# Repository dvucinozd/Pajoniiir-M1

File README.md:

# Pajoniiir-M1

Purpose-built Rev A mainboard for the **Pajoniiir standalone dual-deck DJ system**.

This repository contains the live hierarchical KiCad design, electrical and firmware contracts, mechanical evidence, placement/routing screening contracts, local CAD libraries and fail-closed validation tools.

## Current status

**Electrical milestone:** M1-ELEC-B2

**Mechanical milestone:** M1-MECH-B7

**Pre-layout milestone:** M1-PRELAYOUT-B10 - routed ESP32-P4 flash, crystal and external-DCDC feasibility proof

**Schematic structure:** PASS — 15/15 leaf sheets

**KiCad toolchain:** KiCad 10 only; local KiCad 10.0.4 ERC passes with zero violations and CI installs the KiCad 10 stable release

**Manufacturing BOM parity:** PASS — 244 source / 244 exported, 15 DNP, 3 intentional blank footprints

**Board-first mechanical contract:** PASS — display profiles cannot define the PCB outline or mounts

**Display-derived B2-B6 geometry:** historical screening only

**Final placement/routing freeze:** BLOCKED — 12 physical/EVT gates remain

**Gerber/EVT order:** NOT AUTHORIZED

Evidence updates: [ERC/library closure](docs/Pajoniiir_M1_ERC_Library_Closure_2026-09-04.md), [DSI506 rear image and corrected height](docs/Pajoniiir_M1_DSI506_Evidence_2026-09-04.md).

The current human-readable snapshot is [Pajoniiir M1 Current Design Status B10](docs/Pajoniiir_M1_Current_Design_Status_B10.md).

## Architecture

```text
                         5 V LOCKING INPUT
                                |
                         TPS259474 eFuse
                                |
                         5V_PROTECTED
                                |
                    5 mOhm Kelvin system shunt
                       / INA238 measurement
                                |
                             5V_SYS
              +-----------------+------------------+
              |                                    |
          TPS62132                         USB VBUS switches
          3V3_SYS                          TPS25221 x2
              |                               |       |
      +-------+---------+                  USB0 HS  USB1 FS
      |       |         |                  storage   FLX4
      v       v         v
  ESP32-P4 ESP32-C6  PCM5102A
      |      SDIO      MAIN L/R
      |
      +-- 15-pin MIPI DSI + I2C --> qualified display profile
      +-- SDMMC -----------------> microSD
```

The mainboard exposes a generic 15-pin Raspberry-Pi-style MIPI DSI host interface. EYOYO DSI506 / DYL0023 is the first validated display profile; other models may use the same board after electrical, power, firmware and cable qualification.

## Electrical baseline

- ESP32-P4NRW32X, target silicon v3.2 or newer approved revision
- 32 MB in-package PSRAM
- W25Q128JVPIQ 16 MB external QSPI flash
- ESP32-C6-WROOM-1-N4 over four-bit SDIO
- USB0 dedicated High-Speed storage host
- USB1 GPIO26/27 Full-Speed DDJ-FLX4 MIDI/UAC host
- independent TPS25221 VBUS switching, about 1.0 A USB0 and 1.6 A USB1 initial limits
- PCM5102APWR stereo MAIN output with deterministic XSMT boot mute
- native four-bit SDMMC microSD with TPS22918 power cycling
- P4 UART, P4 USB Serial/JTAG pogo and C6 recovery paths
- optional INA238 system power telemetry

## DSI host contract

```text
Host connector    Amphenol SFW15R-2STE1LF
Interface         15 contacts, 1.0 mm, Raspberry-Pi-style DSI map
Supply branch     3V3_DISPLAY_MODULE; final multi-model budget open
DSI routing       clock + lane0 + lane1
I2C               GPIO7 SDA / GPIO8 SCL
Cable             qualified per display model or adapter
Validated profile DSI506 / DYL0023: lane0, 800 Mbps, RGB888, 27.777 MHz
```

Connector shape alone does not prove compatibility. Every supported display needs a recorded pin map, power envelope, DSI timing/controller profile and cable orientation.

## Mechanical baseline

The mainboard is a standalone assembly and mounts to its own chassis or enclosure bosses. Its outline, mounting pattern and connector coordinates remain open until complete footprint packing, routing, thermal and service-envelope work establishes a viable board.

DSI506-derived values such as the 58 x 49 mm rear posts, 104 x 62 mm board screen and 128 x 84 x 30 mm enclosure screen are retained only for optional DSI506 bracket/enclosure work. They are not production `Edge.Cuts` authority.

## Connector and footprint state

| RefDes | Production part | Footprint | Mechanical state |
|---|---|---|---|
| J1 | Switchcraft 722RAHLP | open | terminal-center and panel geometry required |
| J2/J3 | Amphenol 87520-1010ALF | locked | panel/cable envelope open |
| J4/J5 | Kycon KLPX-0848A-2-W-G / -R-G | locked | panel/cable envelope open |
| J6 | Amphenol SFW15R-2STE1LF | locked | board-edge placement, power budget and per-display cable profile open |
| J7 | Molex 503398-1892 | locked | slot/access/clearance open |
| SW1/SW2 | B3U-3000P-B | locked | recessed tool-hole placement open |
| J9 | project-local factory pogo | closed, DNL | normal placement work only |

Only `J1`, `C3` and `C8` intentionally have blank footprints in the manufacturing source.

## PCB and routing state

`hardware/Pajoniiir-M1/Pajoniiir-M1.kicad_pcb` is a populated four-copper-layer pre-layout canvas. It contains all 244 assigned footprints and 193 named schematic nets in eight `Dwgs.User` working domains. B10 adds 78 track segments and 11 vias for the P4 external flash, crystal and external-DCDC proof. The P4 group has no footprint bounding-box overlaps; the board still has no zones or `Edge.Cuts`.

`m1_board_packing_inventory_b7.json` records all 247 schematic components, 244 assigned footprints, 33 footprint classes including the blank-gate class, and the seven board-first packing phases.

`m1_board_placement_seed_b8.json` records the generated domain coordinates and explicitly marks every coordinate as non-production. The seed and validator scripts preserve schematic UUID paths so KiCad can continue synchronizing the board with the hierarchy.

`m1_prelayout_b9_core_island.json` remains the reproducible unrouted source placement. `m1_prelayout_b10_core_routes.json` records the live critical routes and metrics. Its validator enforces the 5.203 mm U1/Y1 body gap, QSPI transition topology, 0.60/0.30 mm B10 vias, power-trunk widths, zero P4 bounding-box overlaps and zero route-geometry DRC violations.

The stackup is locked to JLCPCB `JLC04161H-7628`, 1.6 mm, 1 oz outer copper and 0.5 oz inner copper.

```text
F.Cu   components + critical USB/MIPI/QSPI/SDIO routing
In1.Cu continuous solid GND reference
In2.Cu power distribution + compatible low-speed routing
B.Cu   secondary components and low-speed routing
```

B5 locks routing topology and provides screening geometry:

- USB: 90 ohm differential; screening 0.2332 mm width / 0.15 mm gap
- MIPI: 100 ohm differential; screening 0.1722 mm width / 0.15 mm gap

These numbers are not production impedance locks. Exact JLCPCB calculator records, soldermask/model selection and matching KiCad rules are required before route freeze.

## Open layout blockers

The current 12 blocking gates are:

```text
C3_INPUT_BULK
C8_PROTECTED_BULK
J1_POWER_INPUT
SW1_RESET
SW2_BOOT
J2_USB0
J3_USB1
J4_RCA_L
J5_RCA_R
J_LCD_DISPLAY_FPC
J7_MICROSD
PCB_OUTLINE
```

Although most connector MPNs and footprints are locked, their gates stay open until absolute panel datums, cutouts, mating envelopes and local clearances are physically validated.

## Repository structure

```text
docs/                         engineering and status documents
hardware/Pajoniiir-M1/        KiCad project and machine contracts
  *.kicad_sch                 root plus 15 hierarchical sheets
  Pajoniiir-M1.kicad_pcb      populated four-layer B10 critical-route canvas
  *.json                      electrical/mechanical/freeze authorities
  libraries/                  project symbols and footprints
  tools/                      migration and fail-closed validators
.github/workflows/            KiCad and mechanical CI
```

## Authority order

When sources disagree:

1. live `hardware/Pajoniiir-M1/*.kicad_sch`
2. `board_first_mechanical_contract.json` and `mechanical_gates.json`
3. `pcb_constraints.json` and the current routing contract
4. B4 exact connector source lock
5. display compatibility profiles, beginning with `display_compatibility_dsi506.json`
6. [Engineering BOM v0.3](docs/Pajoniiir_Mainboard_BOM_v0.3.md)
7. [Global GPIO allocation](docs/Pajoniiir_Global_GPIO_Allocation_v0.1.md)
8. subsystem documents
9. superseded display-mounted B2-B6 and JC4880 records as historical evidence

## Current documents

### Status and release gates

- [Development handoff and remaining work](docs/Pajoniiir_M1_Development_Handoff_2026-09-08.md)
- [Current Design Status B10](docs/Pajoniiir_M1_Current_Design_Status_B10.md)
- [B10 P4 Critical Routes](docs/Pajoniiir_M1_PRELAYOUT_B10_P4_Critical_Routes_v0.1.md)
- [B9 P4 Core Island](docs/Pajoniiir_M1_PRELAYOUT_B9_P4_Core_Island_v0.1.md)
- [Schematic Audit](docs/Pajoniiir_M1_Schematic_Audit_v0.1.md)
- [Schematic Readiness Review](docs/Pajoniiir_RevA_Schematic_Readiness_Review_v0.1.md)
- [Manufacturing Output Contract](docs/Pajoniiir_Manufacturing_Output_Contract_v0.1.md)
- [Mechanical and Sourcing Gates](docs/Pajoniiir_M1_Mechanical_Sourcing_Gates_v0.1.md)
- [PCB Placement and Routing Constraints](docs/Pajoniiir_M1_PCB_Layout_Constraints_v0.1.md)

### Electrical contracts

- [Engineering BOM v0.3](docs/Pajoniiir_Mainboard_BOM_v0.3.md)
- [Global GPIO Allocation](docs/Pajoniiir_Global_GPIO_Allocation_v0.1.md)
- [Hardware/Firmware Contract](docs/Pajoniiir_M1_Hardware_Firmware_Contract_v0.1.md)
- [5-inch DSI Interface Migration](docs/Pajoniiir_M1_ELEC_B0_5in_DSI_Interface_Migration_v0.1.md)
- [15-pin DSI Connector Lock](docs/Pajoniiir_M1_ELEC_B1_DSI15_Connector_Lock_v0.1.md)
- [Board-first mechanical rebase](docs/Pajoniiir_M1_MECH_B7_Board_First_Rebase_v0.1.md)
- [DSI506 compatibility evidence](docs/Pajoniiir_M1_DSI506_Evidence_2026-09-04.md)

### Historical and subsystem design records

The original architecture, schematic plan, JC4880 display/backlight, GT911 and M1-MECH-A documents remain in `docs/` as design provenance. Their display-specific geometry does not override the B7 board-first authority.

## Validation

From the repository root:

```bash
python hardware/Pajoniiir-M1/tools/validate_schematic_structure.py
python hardware/Pajoniiir-M1/tools/validate_mechanical_authority.py
python hardware/Pajoniiir-M1/tools/report_mech_gate_snapshot.py
"C:/Program Files/KiCad/10.0/bin/python.exe" hardware/Pajoniiir-M1/tools/validate_core_routing_b10.py \
  --board hardware/Pajoniiir-M1/Pajoniiir-M1.kicad_pcb \
  --project hardware/Pajoniiir-M1/Pajoniiir-M1.kicad_pro \
  --report hardware/Pajoniiir-M1/m1_prelayout_b10_core_routes.json \
  --drc <fresh-kicad-drc.json>
```

Native KiCad 10 CI loads every schematic, exports and cross-checks the manufacturing BOM, exports the hierarchy netlist/PDF, enforces ERC cleanliness and validates the B10 PCB routing contract against a fresh DRC report.

Final placement, routing, Gerbers and EVT ordering remain blocked until every `blocks_layout_freeze` gate is closed and the production impedance geometry is recorded.

## Native Rust firmware foundation

The M1 software rewrite is developed in `firmware-rust/`. The released Pajoniiir M2.2 firmware is the functional/product golden reference; this repository's live hardware contracts remain the electrical authority.

Current Rust architecture decisions:

- native `no_std` ESP32-P4 product direction;
- Slint for UI;
- dedicated RGB565 Rust waveform renderer with embedded-graphics for suitable primitives;
- data-driven multi-controller profiles;
- provider-neutral TrackAnalysis for Rekordbox/APTA;
- host-first regression and desktop simulation before M1 EVT hardware exists.

References:

- [M1 Rust Product Requirements](docs/M1_RUST_PRODUCT_REQUIREMENTS.md)
- [M1 Rust Architecture](docs/M1_RUST_ARCHITECTURE.md)
- [Architecture Decision Records](docs/adr/)
- [Rust workspace](firmware-rust/README.md)

Rust host/simulator success does not close any physical PCB, USB, audio, DSI, PSRAM/DMA, C6 or power qualification gate.

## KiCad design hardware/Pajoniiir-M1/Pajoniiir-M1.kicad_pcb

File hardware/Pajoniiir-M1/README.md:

# Pajoniiir-M1 KiCad Rev A

Live KiCad 10 project for the Pajoniiir-M1 custom mainboard. KiCad 10 is the only supported ECAD toolchain for future edits and CI.

## Current design state

- Electrical milestone: M1-ELEC-B2
- Mechanical milestone: M1-MECH-B7
- Pre-layout milestone: M1-PRELAYOUT-B10 P4 critical-route proof
- Root schematic plus 15 leaf sheets: structurally clean
- Current manufacturing source: 244 `in_bom=yes`, 15 DNP, 3 intentional blank footprints
- PCB: 244 footprints, 193 named nets, 78 B10 track segments and 11 vias; no zones/`Edge.Cuts`
- Board packing inventory: 247 schematic components, 244 assigned footprints, 3 intentional blanks
- Final placement/routing freeze: blocked by 12 physical/EVT gates

J6 is a generic 15-pin Raspberry-Pi-style MIPI DSI host using Amphenol SFW15R-2STE1LF. DSI506 / DYL0023 is one validated display profile. `11_TOUCH_GT911.kicad_sch` stays empty because touch behavior belongs to the selected display profile.

## Authorities

1. `*.kicad_sch` — connectivity, RefDes, values and footprints
2. `board_first_mechanical_contract.json` — mainboard geometry boundary
3. `mechanical_gates.json` and `pcb_constraints.json` — freeze and layout gates
4. `m1_prelayout_b5_routing_contract.json` — routing topology and impedance state
5. `m1_board_packing_inventory_b7.json` — footprint population and packing sequence
6. `m1_board_placement_seed_b8.json` — populated-domain coordinates and non-production boundary
7. `m1_prelayout_b9_core_island.json` — reproducible unrouted P4 source placement
8. `m1_prelayout_b10_core_routes.json` — current critical-route placement and copper metrics
9. `m1_mech_b4_connector_source_lock.json` — exact external connector intent
10. `display_compatibility_dsi506.json` — first qualified display profile

The B2-B6 display-mounted placement and enclosure JSON files are retained as historical DSI506 screening only.

Human-readable current state: `../../docs/Pajoniiir_M1_Current_Design_Status_B10.md`.

Next-session development sequence: `../../docs/Pajoniiir_M1_Development_Handoff_2026-09-08.md`.

## Mechanical and routing boundary

The board mounts to its own chassis. Final `Edge.Cuts`, chassis holes, connector coordinates and height zones must come from board component packing, routing and service requirements. Display rear posts and display-derived board/enclosure screens are not production authority.

The selected stackup is JLCPCB JLC04161H-7628, four layers and 1.6 mm. Exact 90 ohm USB and 100 ohm MIPI width/gap values still require a recorded JLCPCB calculator result before routing freeze.

Do not add production `Edge.Cuts`, call screening anchors final placement, or release Gerbers while `layout_freeze_allowed` is false.

## Validation

Run from the repository root:

```bash
python hardware/Pajoniiir-M1/tools/validate_schematic_structure.py
python hardware/Pajoniiir-M1/tools/validate_mechanical_authority.py
python hardware/Pajoniiir-M1/tools/validate_board_packing_inventory.py
python hardware/Pajoniiir-M1/tools/report_mech_gate_snapshot.py
"C:/Program Files/KiCad/10.0/bin/python.exe" hardware/Pajoniiir-M1/tools/validate_core_routing_b10.py \
  --board hardware/Pajoniiir-M1/Pajoniiir-M1.kicad_pcb \
  --project hardware/Pajoniiir-M1/Pajoniiir-M1.kicad_pro \
  --report hardware/Pajoniiir-M1/m1_prelayout_b10_core_routes.json \
  --drc <fresh-kicad-drc.json>
```

Native KiCad ERC, hierarchy load, manufacturing BOM parity, netlist and PDF export are enforced in CI. B10 routing validation additionally uses KiCad's bundled `pcbnew` Python module and a fresh KiCad DRC JSON locally.

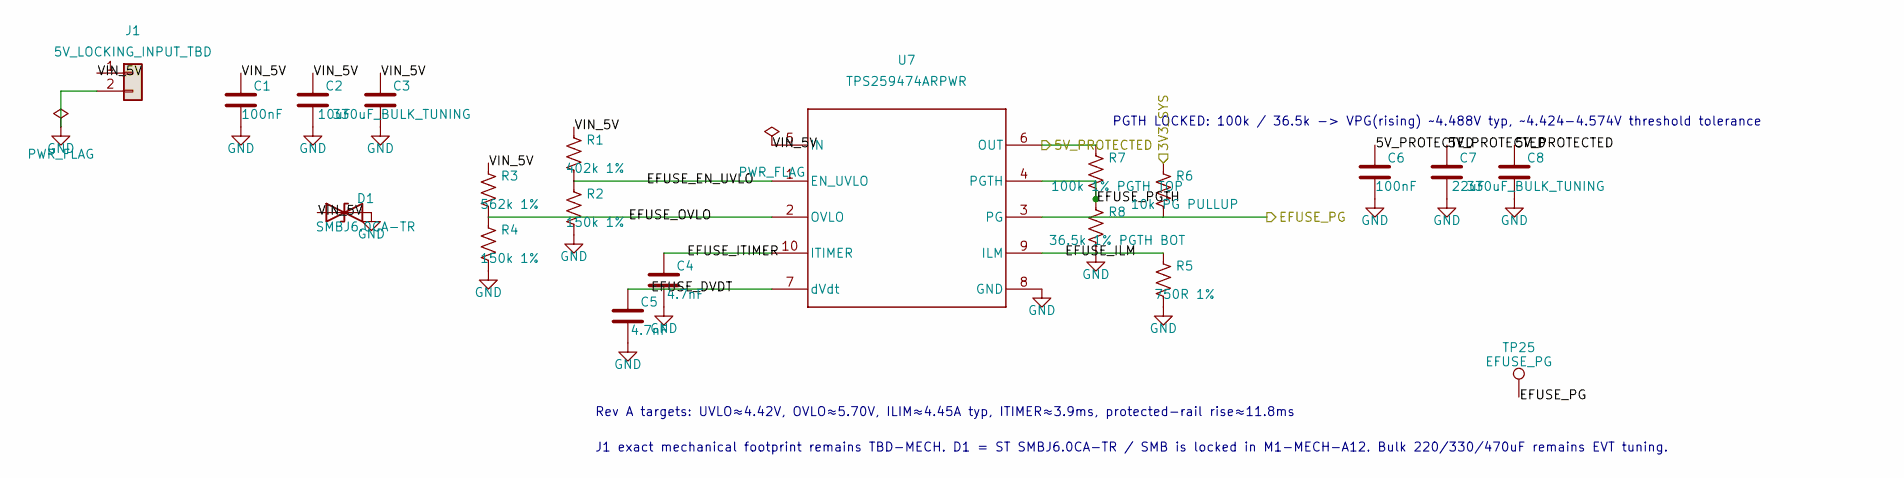
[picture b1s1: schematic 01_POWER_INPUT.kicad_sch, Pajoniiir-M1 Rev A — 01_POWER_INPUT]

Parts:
C1, C6: 100nF; C_0603_1608Metric
C2: 10uF; C_0805_2012Metric
C3, C8: 330uF_BULK_TUNING
C4, C5: 4.7nF; C_0603_1608Metric
C7: 22uF; C_1206_3216Metric
D1: SMBJ6.0CA-TR; D_SMB
J1: 5V_LOCKING_INPUT_TBD
R1: 402k 1%; R_0603_1608Metric
R2, R4: 150k 1%; R_0603_1608Metric
R3: 562k 1%; R_0603_1608Metric
R5: 750R 1%; R_0603_1608Metric
R6: 10k PG PULLUP; R_0603_1608Metric
R7: 100k 1% PGTH TOP; R_0603_1608Metric
R8: 36.5k 1% PGTH BOT; R_0603_1608Metric
TP25: EFUSE_PG; TestPoint_Pad_D1.5mm
U7: TPS259474ARPWR; Texas_RPW0010A_VQFN-HR-10_2x2mm; MPN TPS259474ARPWR

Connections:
/01_POWER_INPUT/EFUSE_DVDT: C5.1, U7.7 (dVdt)
/01_POWER_INPUT/EFUSE_EN_UVLO: R1.2, R2.1, U7.1 (EN_UVLO)
/01_POWER_INPUT/EFUSE_ITIMER: C4.1, U7.10 (ITIMER)
/01_POWER_INPUT/EFUSE_OVLO: R3.2, R4.1, U7.2 (OVLO)
/01_POWER_INPUT/EFUSE_PG: R6.2, TP25.1, U7.3 (PG)
/01_POWER_INPUT/EFUSE_PGTH: R7.2, R8.1, U7.4 (PGTH)
/01_POWER_INPUT/VIN_5V: C1.1, C2.1, C3.1, D1.1 (A1), J1.1, R1.1, R3.1, U7.5 (IN)
/3V3_SYS: R6.1; also elsewhere on the board
/5V_PROTECTED: C6.1, C7.1, C8.1, R7.1, U7.6 (OUT); also elsewhere on the board

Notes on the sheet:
PGTH LOCKED: 100k / 36.5k -> VPG(rising) ~4.488V typ, ~4.424-4.574V threshold tolerance
Rev A targets: UVLO≈4.42V, OVLO≈5.70V, ILIM≈4.45A typ, ITIMER≈3.9ms, protected-rail rise≈11.8ms
J1 exact mechanical footprint remains TBD-MECH. D1 = ST SMBJ6.0CA-TR / SMB is locked in M1-MECH-A12. Bulk 220/330/470uF remains EVT tuning.

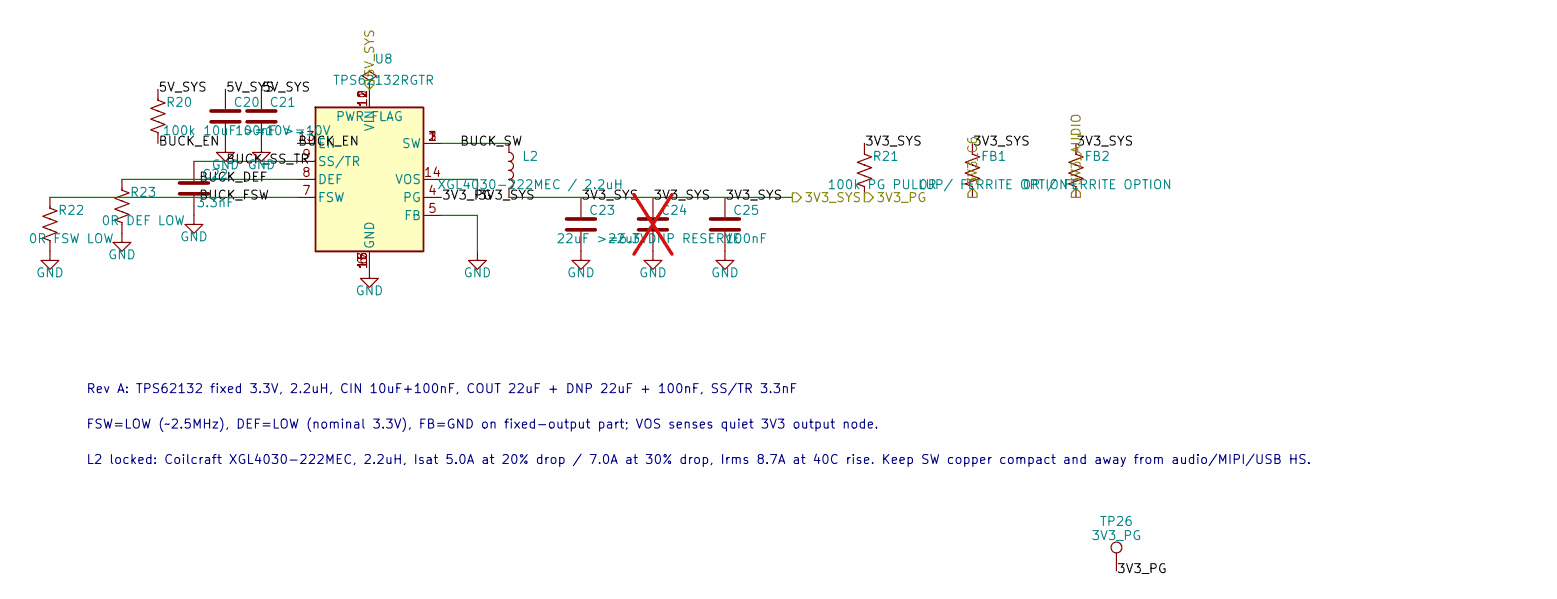
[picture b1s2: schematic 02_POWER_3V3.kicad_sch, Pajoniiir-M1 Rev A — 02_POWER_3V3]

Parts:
C20: 10uF >=10V; C_0805_2012Metric
C21: 100nF >=10V; C_0603_1608Metric
C22: 3.3nF; C_0603_1608Metric
C23: 22uF >=6.3V; C_1206_3216Metric
C24: 22uF DNP RESERVE; C_1206_3216Metric; not fitted
C25: 100nF; C_0603_1608Metric
FB1, FB2: 0R / FERRITE OPTION; R_0603_1608Metric
L2: XGL4030-222MEC / 2.2uH; L_Coilcraft_XxL4030
R20: 100k; R_0603_1608Metric
R21: 100k PG PULLUP; R_0603_1608Metric
R22: 0R FSW LOW; R_0603_1608Metric
R23: 0R DEF LOW; R_0603_1608Metric
TP26: 3V3_PG; TestPoint_Pad_D1.5mm
U8: TPS62132RGTR; VQFN-16-1EP_3x3mm_P0.5mm_EP1.68x1.68mm_ThermalVias

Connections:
/02_POWER_3V3/3V3_PG: R21.2, TP26.1, U8.4 (PG)
/02_POWER_3V3/BUCK_DEF: R23.1, U8.8 (DEF)
/02_POWER_3V3/BUCK_EN: R20.2, U8.13 (EN)
/02_POWER_3V3/BUCK_FSW: R22.1, U8.7 (FSW)
/02_POWER_3V3/BUCK_SS_TR: C22.1, U8.9 (SS/TR)
/02_POWER_3V3/BUCK_SW: L2.1, U8.1 (SW), U8.2 (SW), U8.3 (SW)
/3V3_AUDIO: FB2.2; also elsewhere on the board
/3V3_C6: FB1.2; also elsewhere on the board
/3V3_SYS: C23.1, C24.1, C25.1, FB1.1, FB2.1, L2.2, R21.1, U8.14 (VOS); also elsewhere on the board
/5V_SYS: C20.1, C21.1, R20.1, U8.10 (VIN), U8.11 (VIN), U8.12 (VIN); also elsewhere on the board

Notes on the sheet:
Rev A: TPS62132 fixed 3.3V, 2.2uH, CIN 10uF+100nF, COUT 22uF + DNP 22uF + 100nF, SS/TR 3.3nF
FSW=LOW (~2.5MHz), DEF=LOW (nominal 3.3V), FB=GND on fixed-output part; VOS senses quiet 3V3 output node.
L2 locked: Coilcraft XGL4030-222MEC, 2.2uH, Isat 5.0A at 20% drop / 7.0A at 30% drop, Irms 8.7A at 40C rise. Keep SW copper compact and away from audio/MIPI/USB HS.

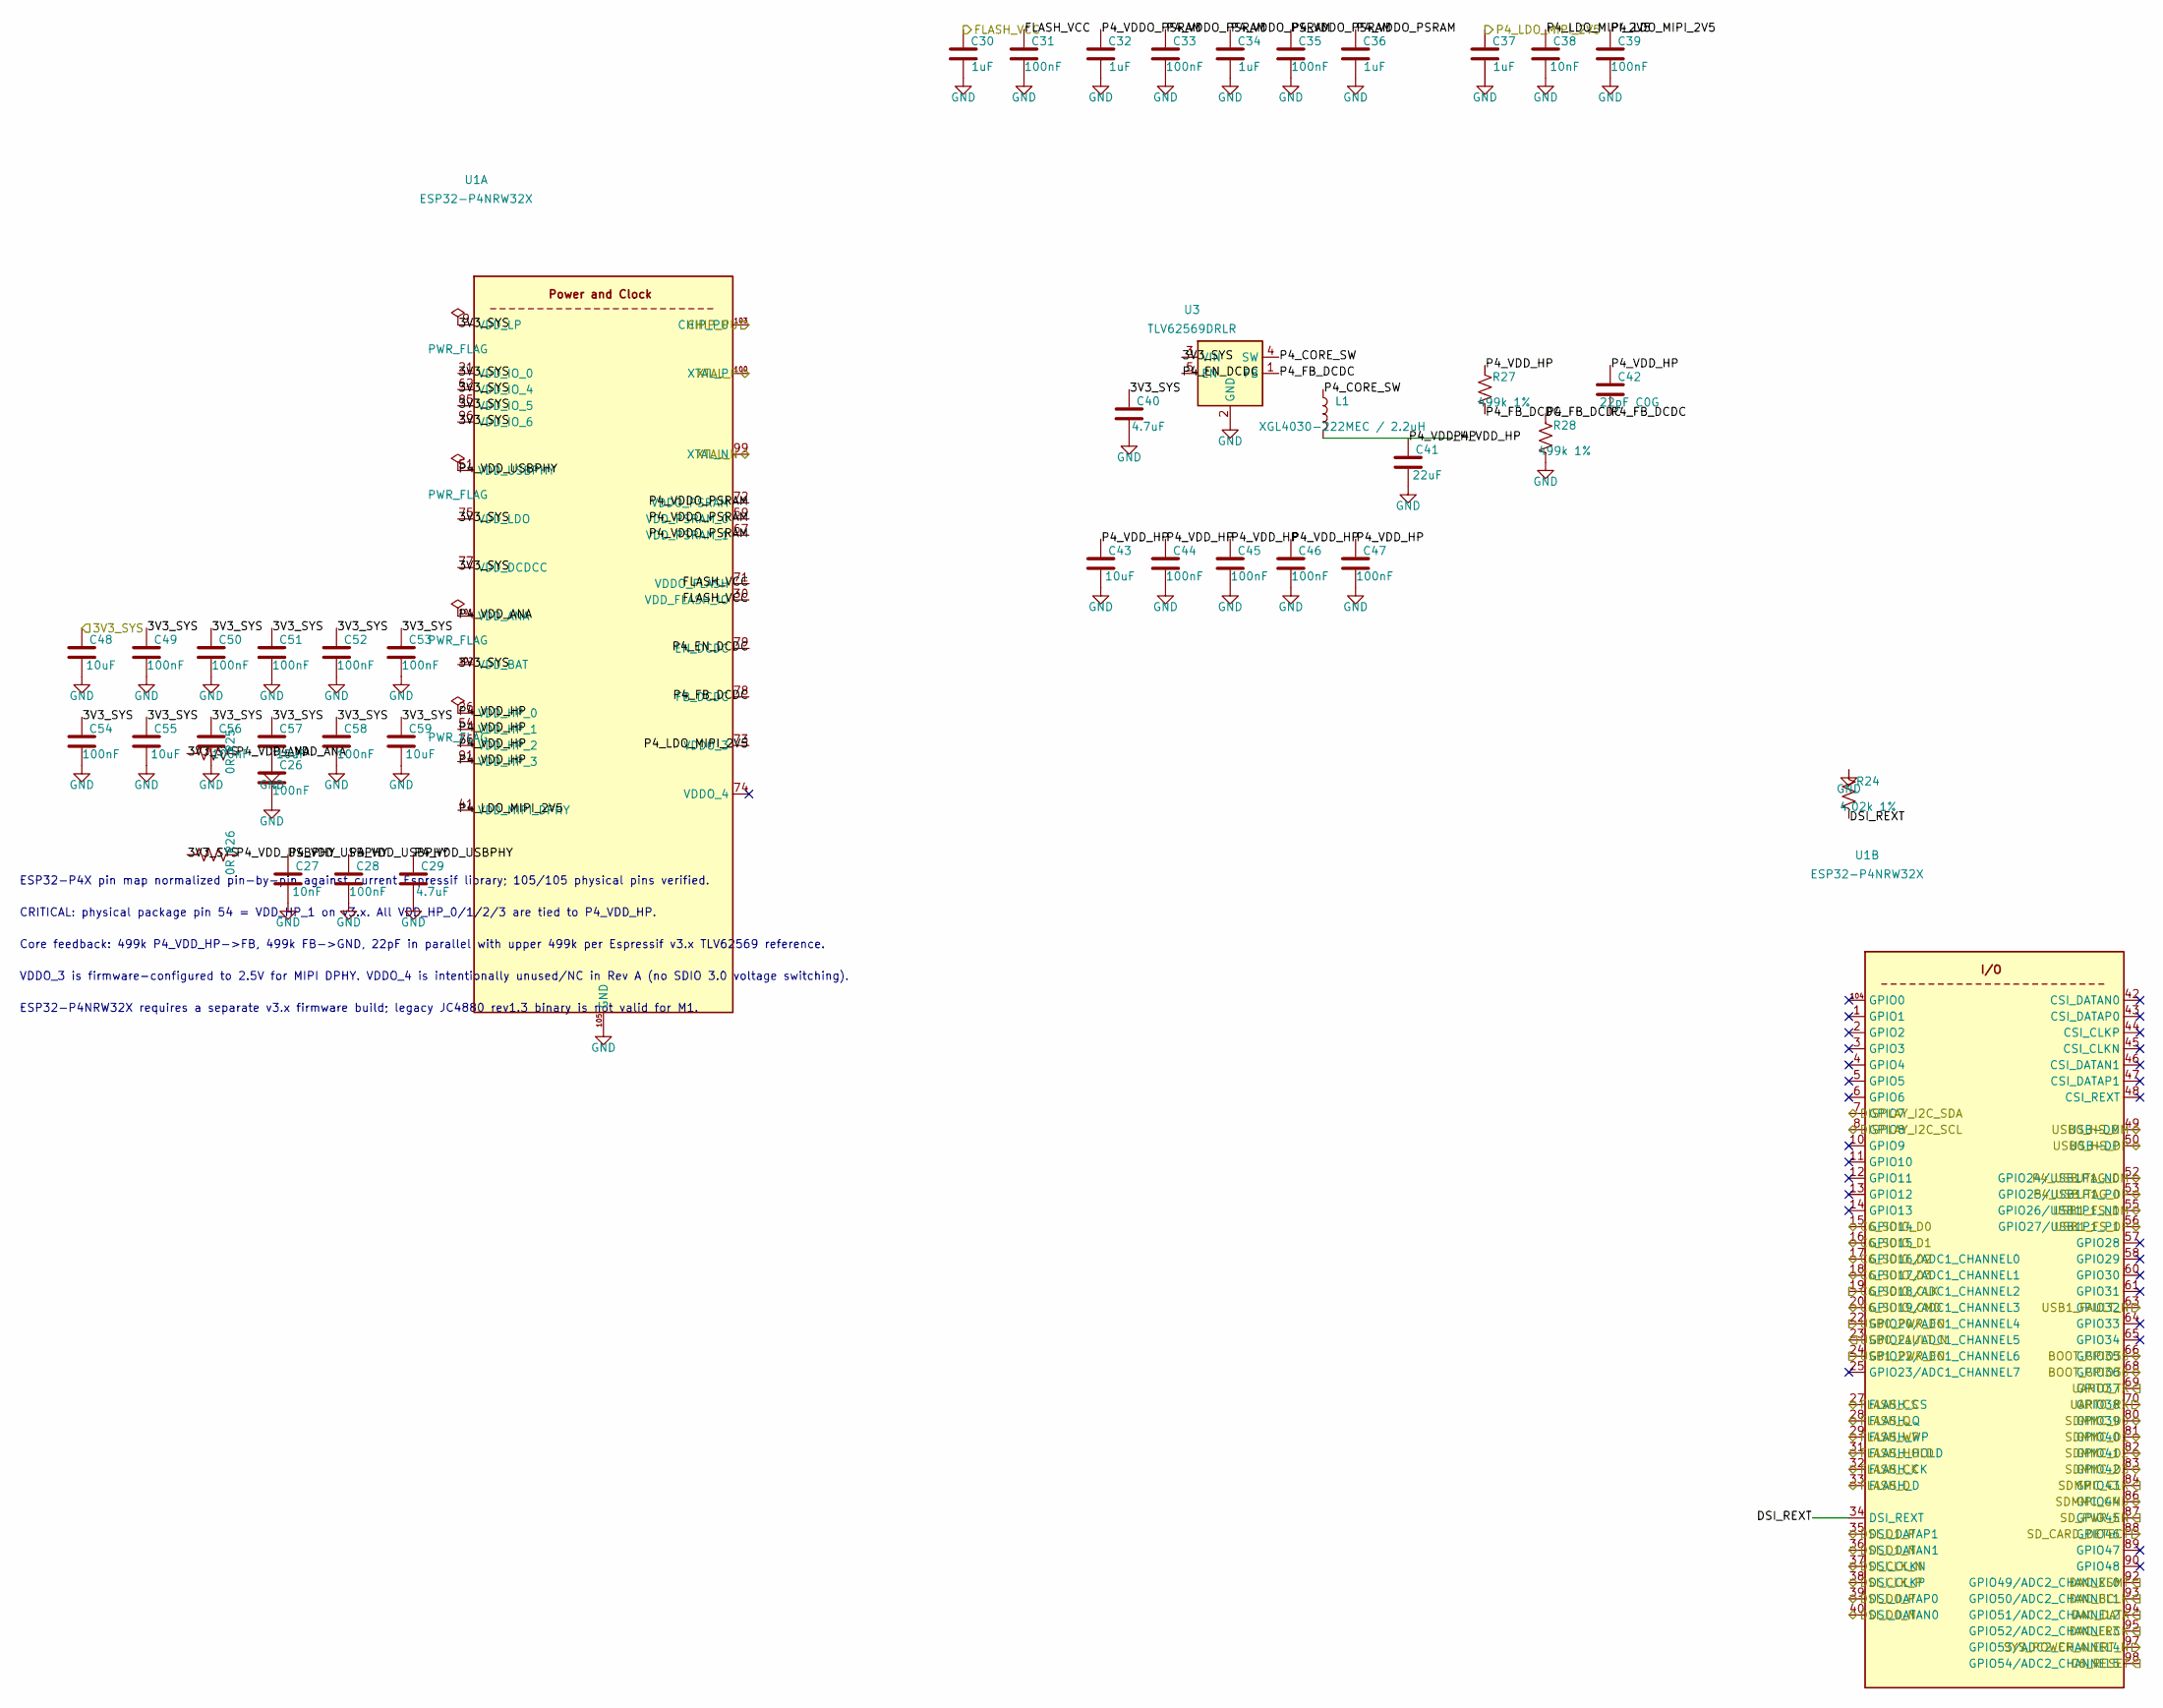
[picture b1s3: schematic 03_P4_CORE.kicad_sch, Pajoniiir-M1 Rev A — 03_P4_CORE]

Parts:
C26, C28, C31, C33, C35, C39, C44, C45, C46, C47, C49, C50, C51, C52, C53, C54, C56, C58: 100nF; C_0603_1608Metric
C27, C38: 10nF; C_0402_1005Metric
C29: 4.7uF; C_0603_1608Metric
C30, C32, C34, C36, C37: 1uF; C_0603_1608Metric
C40: 4.7uF; C_0805_2012Metric
C41: 22uF; C_0805_2012Metric
C42: 22pF C0G; C_0402_1005Metric
C43, C48, C55, C57, C59: 10uF; C_0805_2012Metric
L1: XGL4030-222MEC / 2.2uH; L_Coilcraft_XxL4030
R24: 4.02k 1%; R_0402_1005Metric
R25, R26: 0R; R_0603_1608Metric
R27, R28: 499k 1%; R_0402_1005Metric
U1: ESP32-P4NRW32X; ESP32-P4
U3: TLV62569DRLR; SOT-563

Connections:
/3V3_SYS: C40.1, C48.1, C49.1, C50.1, C51.1, C52.1, C53.1, C54.1, C55.1, C56.1, C57.1, C58.1, C59.1, R25.1, R26.1, U1.9 (VDD_LP), U1.21 (VDD_IO_0), U1.62 (VDD_IO_4), U1.75 (VDD_LDO), U1.77 (VDD_DCDCC), U1.85 (VDD_IO_5), U1.96 (VDD_IO_6), U1.102 (VDD_BAT), U3.3 (VIN); also elsewhere on the board
/03_P4_CORE/DSI_REXT: R24.2, U1.34 (DSI_REXT)
/03_P4_CORE/FLASH_CK: U1.32 (FLASH_CK); also elsewhere on the board
/03_P4_CORE/FLASH_D: U1.33 (FLASH_D); also elsewhere on the board
/03_P4_CORE/FLASH_HOLD: U1.31 (FLASH_HOLD); also elsewhere on the board
/03_P4_CORE/FLASH_Q: U1.28 (FLASH_Q); also elsewhere on the board
/03_P4_CORE/FLASH_VCC: C30.1, C31.1, U1.30 (VDD_FLASH_IO), U1.71 (VDDO_FLASH); also elsewhere on the board
/03_P4_CORE/FLASH_WP: U1.29 (FLASH_WP); also elsewhere on the board
/03_P4_CORE/P4_CORE_SW: L1.1, U3.4 (SW)
/03_P4_CORE/P4_EN_DCDC: U1.79 (EN_DCDC), U3.5 (EN)
/03_P4_CORE/P4_FB_DCDC: C42.2, R27.2, R28.1, U1.78 (FB_DCDC), U3.1 (FB)
/03_P4_CORE/P4_VDDO_PSRAM: C32.1, C33.1, C34.1, C35.1, C36.1, U1.59 (VDD_PSRAM_0), U1.67 (VDD_PSRAM_1), U1.72 (VDDO_PSRAM)
/03_P4_CORE/P4_VDD_ANA: C26.1, R25.2, U1.101 (VDD_ANA)
/03_P4_CORE/P4_VDD_HP: C41.1, C42.1, C43.1, C44.1, C45.1, C46.1, C47.1, L1.2, R27.1, U1.26 (VDD_HP_0), U1.54 (VDD_HP_1), U1.76 (VDD_HP_2), U1.91 (VDD_HP_3)
/03_P4_CORE/P4_VDD_USBPHY: C27.1, C28.1, C29.1, R26.2, U1.51 (VDD_USBPHY)
/04_P4_FLASH_CLOCK_RESET/FLASH_CS: U1.27 (FLASH_CS); also elsewhere on the board
/BOOT_GPIO35: U1.66 (GPIO35); also elsewhere on the board
/BOOT_GPIO36: U1.68 (GPIO36); also elsewhere on the board
/C6_RESET: U1.98 (GPIO54/ADC2_CHANNEL5); also elsewhere on the board
/C6_SDIO_CLK: U1.19 (GPIO18/ADC1_CHANNEL2); also elsewhere on the board
/C6_SDIO_CMD: U1.20 (GPIO19/ADC1_CHANNEL3); also elsewhere on the board
/C6_SDIO_D0: U1.15 (GPIO14); also elsewhere on the board
/C6_SDIO_D1: U1.16 (GPIO15); also elsewhere on the board
/C6_SDIO_D2: U1.17 (GPIO16/ADC1_CHANNEL0); also elsewhere on the board
/C6_SDIO_D3: U1.18 (GPIO17/ADC1_CHANNEL1); also elsewhere on the board
/CHIP_PU: U1.103 (CHIP_PU); also elsewhere on the board
/DAC_BCLK: U1.93 (GPIO50/ADC2_CHANNEL1); also elsewhere on the board
/DAC_DATA: U1.94 (GPIO51/ADC2_CHANNEL2); also elsewhere on the board
/DAC_LRCK: U1.95 (GPIO52/ADC2_CHANNEL3); also elsewhere on the board
/DAC_XSMT: U1.92 (GPIO49/ADC2_CHANNEL0); also elsewhere on the board
/DISPLAY_I2C_SCL: U1.8 (GPIO8); also elsewhere on the board
/DISPLAY_I2C_SDA: U1.7 (GPIO7); also elsewhere on the board
/DSI_CLK_N: U1.37 (DSI_CLKN); also elsewhere on the board
/DSI_CLK_P: U1.38 (DSI_CLKP); also elsewhere on the board
/DSI_D0_N: U1.40 (DSI_DATAN0); also elsewhere on the board
/DSI_D0_P: U1.39 (DSI_DATAP0); also elsewhere on the board
/DSI_D1_N: U1.36 (DSI_DATAN1); also elsewhere on the board
/DSI_D1_P: U1.35 (DSI_DATAP1); also elsewhere on the board
/P4_LDO_MIPI_2V5: C37.1, C38.1, C39.1, U1.41 (VDD_MIPI_DPHY), U1.73 (VDDO_3); also elsewhere on the board
/P4_USBJTAG_DM: U1.52 (GPIO24/USB1P1_N0); also elsewhere on the board
/P4_USBJTAG_DP: U1.53 (GPIO25/USB1P1_P0); also elsewhere on the board
/SDMMC_CLK: U1.84 (GPIO43); also elsewhere on the board
/SDMMC_CMD: U1.86 (GPIO44); also elsewhere on the board
/SDMMC_D0: U1.80 (GPIO39); also elsewhere on the board
/SDMMC_D1: U1.81 (GPIO40); also elsewhere on the board
/SDMMC_D2: U1.82 (GPIO41); also elsewhere on the board
/SDMMC_D3: U1.83 (GPIO42); also elsewhere on the board
/SD_CARD_DETECT: U1.88 (GPIO46); also elsewhere on the board
/SD_PWR_EN: U1.87 (GPIO45); also elsewhere on the board
/SYS_POWER_ALERT_N: U1.97 (GPIO53/ADC2_CHANNEL4); also elsewhere on the board
/UART0_RX: U1.70 (GPIO38); also elsewhere on the board
/UART0_TX: U1.69 (GPIO37); also elsewhere on the board
/USB0_FAULT_N: U1.23 (GPIO21/ADC1_CHANNEL5); also elsewhere on the board
/USB0_HS_DM: U1.49 (USB-DM); also elsewhere on the board
/USB0_HS_DP: U1.50 (USB-DP); also elsewhere on the board
/USB0_PWR_EN: U1.22 (GPIO20/ADC1_CHANNEL4); also elsewhere on the board
/USB1_FAULT_N: U1.63 (GPIO32); also elsewhere on the board
/USB1_FS_DM: U1.55 (GPIO26/USB1P1_N1); also elsewhere on the board
/USB1_FS_DP: U1.56 (GPIO27/USB1P1_P1); also elsewhere on the board
/USB1_PWR_EN: U1.24 (GPIO22/ADC1_CHANNEL6); also elsewhere on the board
/XTAL_N: U1.99 (XTAL_N); also elsewhere on the board
/XTAL_P: U1.100 (XTAL_P); also elsewhere on the board

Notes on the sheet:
ESP32-P4X pin map normalized pin-by-pin against current Espressif library; 105/105 physical pins verified.
CRITICAL: physical package pin 54 = VDD_HP_1 on v3.x. All VDD_HP_0/1/2/3 are tied to P4_VDD_HP.
Core feedback: 499k P4_VDD_HP->FB, 499k FB->GND, 22pF in parallel with upper 499k per Espressif v3.x TLV62569 reference.
VDDO_3 is firmware-configured to 2.5V for MIPI DPHY. VDDO_4 is intentionally unused/NC in Rev A (no SDIO 3.0 voltage switching).
ESP32-P4NRW32X requires a separate v3.x firmware build; legacy JC4880 rev1.3 binary is not valid for M1.

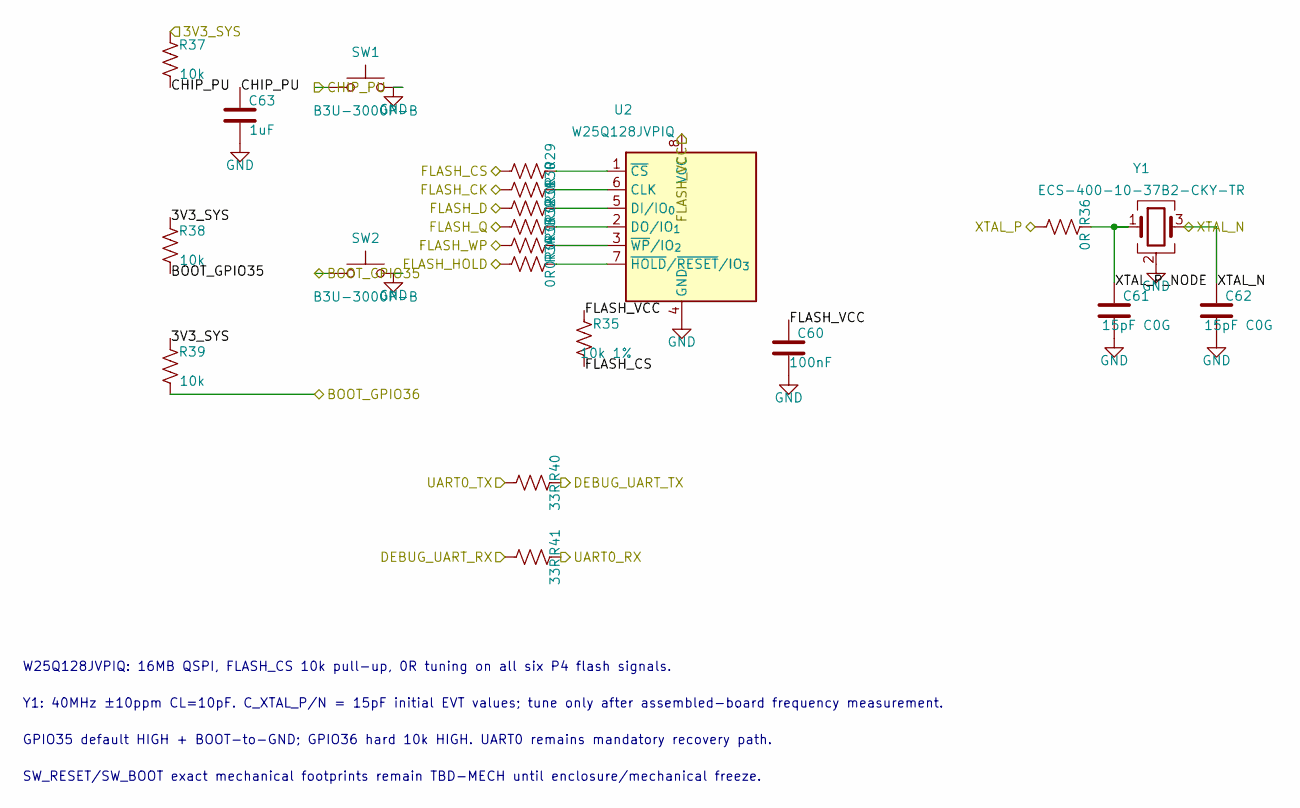
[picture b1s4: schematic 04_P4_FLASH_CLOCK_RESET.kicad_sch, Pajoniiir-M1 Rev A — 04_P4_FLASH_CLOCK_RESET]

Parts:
C60: 100nF; C_0603_1608Metric
C61, C62: 15pF C0G; C_0402_1005Metric
C63: 1uF; C_0603_1608Metric
R29, R30, R31, R32, R33, R34, R36: 0R; R_0402_1005Metric
R35: 10k 1%; R_0603_1608Metric
R37, R38, R39: 10k; R_0603_1608Metric
R40, R41: 33R; R_0603_1608Metric
SW1, SW2: B3U-3000P-B; SW_SPST_B3U-3000P-B
U2: W25Q128JVPIQ; WSON-8-1EP_6x5mm_P1.27mm_EP3.4x4.3mm
Y1: ECS-400-10-37B2-CKY-TR; Crystal_SMD_2016-4Pin_2.0x1.6mm

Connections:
/3V3_SYS: R37.1, R38.1, R39.1; also elsewhere on the board
/03_P4_CORE/FLASH_CK: R30.1; also elsewhere on the board
/03_P4_CORE/FLASH_D: R31.1; also elsewhere on the board
/03_P4_CORE/FLASH_HOLD: R34.1; also elsewhere on the board
/03_P4_CORE/FLASH_Q: R32.1; also elsewhere on the board
/03_P4_CORE/FLASH_VCC: C60.1, R35.1, U2.8 (VCC); also elsewhere on the board
/03_P4_CORE/FLASH_WP: R33.1; also elsewhere on the board
/04_P4_FLASH_CLOCK_RESET/FLASH_CS: R29.1, R35.2; also elsewhere on the board
/04_P4_FLASH_CLOCK_RESET/XTAL_P_NODE: C61.1, R36.2, Y1.1
/BOOT_GPIO35: R38.2, SW2.1; also elsewhere on the board
/BOOT_GPIO36: R39.2; also elsewhere on the board
/CHIP_PU: C63.1, R37.2, SW1.1; also elsewhere on the board
/DEBUG_UART_RX: R41.1; also elsewhere on the board
/DEBUG_UART_TX: R40.2; also elsewhere on the board
/UART0_RX: R41.2; also elsewhere on the board
/UART0_TX: R40.1; also elsewhere on the board
/XTAL_N: C62.1, Y1.3; also elsewhere on the board
/XTAL_P: R36.1; also elsewhere on the board
unnamed: R30.2, U2.6 (CLK)
unnamed: R31.2, U2.5 (DI/IO_{0})
unnamed: R32.2, U2.2 (DO/IO_{1})
unnamed: R29.2, U2.1 (~CS)
unnamed: R34.2, U2.7 (~HOLD/~RESET/IO_{3})
unnamed: R33.2, U2.3 (~WP/IO_{2})

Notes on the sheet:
W25Q128JVPIQ: 16MB QSPI, FLASH_CS 10k pull-up, 0R tuning on all six P4 flash signals.
Y1: 40MHz ±10ppm CL=10pF. C_XTAL_P/N = 15pF initial EVT values; tune only after assembled-board frequency measurement.
GPIO35 default HIGH + BOOT-to-GND; GPIO36 hard 10k HIGH. UART0 remains mandatory recovery path.
SW_RESET/SW_BOOT exact mechanical footprints remain TBD-MECH until enclosure/mechanical freeze.

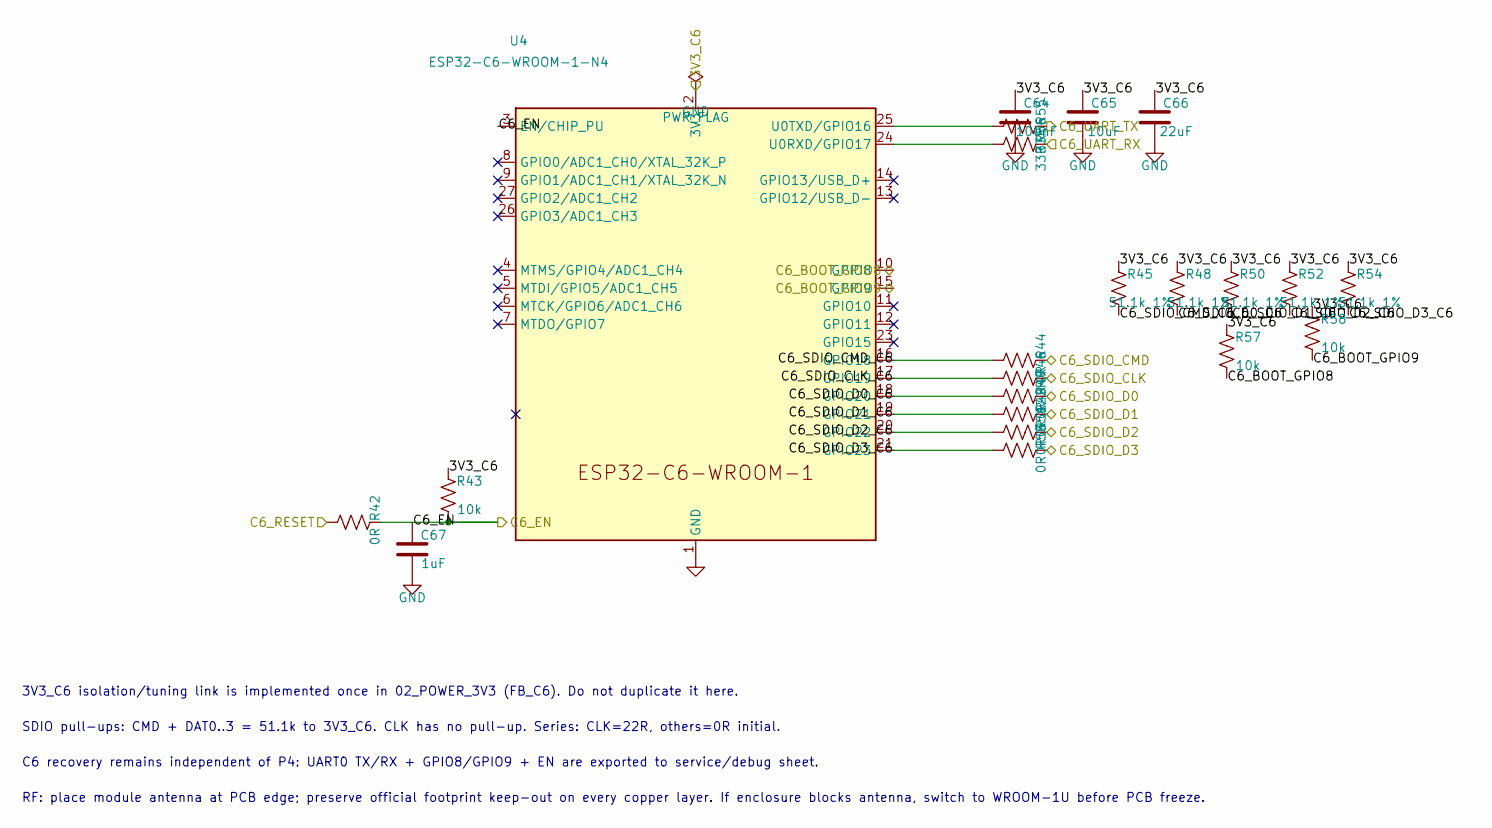
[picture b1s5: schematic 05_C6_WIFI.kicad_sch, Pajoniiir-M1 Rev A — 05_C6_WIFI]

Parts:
C64: 100nF; C_0603_1608Metric
C65: 10uF; C_0805_2012Metric
C66: 22uF; C_1206_3216Metric
C67: 1uF; C_0603_1608Metric
R42: 0R; R_0603_1608Metric
R43, R57, R58: 10k; R_0603_1608Metric
R44, R47, R49, R51, R53: 0R; R_0402_1005Metric
R45, R48, R50, R52, R54: 51.1k 1%; R_0603_1608Metric
R46: 22R; R_0402_1005Metric
R55, R56: 33R; R_0603_1608Metric
U4: ESP32-C6-WROOM-1-N4; ESP32-C6-WROOM-1

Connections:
/3V3_C6: C64.1, C65.1, C66.1, R43.1, R45.1, R48.1, R50.1, R52.1, R54.1, R57.1, R58.1, U4.2 (3V3); also elsewhere on the board
/05_C6_WIFI/C6_SDIO_CLK_C6: R46.1, U4.17 (GPIO19)
/05_C6_WIFI/C6_SDIO_CMD_C6: R44.1, R45.2, U4.16 (GPIO18)
/05_C6_WIFI/C6_SDIO_D0_C6: R47.1, R48.2, U4.18 (GPIO20)
/05_C6_WIFI/C6_SDIO_D1_C6: R49.1, R50.2, U4.19 (GPIO21)
/05_C6_WIFI/C6_SDIO_D2_C6: R51.1, R52.2, U4.20 (GPIO22)
/05_C6_WIFI/C6_SDIO_D3_C6: R53.1, R54.2, U4.21 (GPIO23)
/C6_BOOT_GPIO8: R57.2, U4.10 (GPIO8); also elsewhere on the board
/C6_BOOT_GPIO9: R58.2, U4.15 (GPIO9); also elsewhere on the board
/C6_EN: C67.1, R42.2, R43.2, U4.3 (EN/CHIP_PU); also elsewhere on the board
/C6_RESET: R42.1; also elsewhere on the board
/C6_SDIO_CLK: R46.2; also elsewhere on the board
/C6_SDIO_CMD: R44.2; also elsewhere on the board
/C6_SDIO_D0: R47.2; also elsewhere on the board
/C6_SDIO_D1: R49.2; also elsewhere on the board
/C6_SDIO_D2: R51.2; also elsewhere on the board
/C6_SDIO_D3: R53.2; also elsewhere on the board
/C6_UART_RX: R56.2; also elsewhere on the board
/C6_UART_TX: R55.2; also elsewhere on the board
unnamed: R56.1, U4.24 (U0RXD/GPIO17)
unnamed: R55.1, U4.25 (U0TXD/GPIO16)

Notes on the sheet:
3V3_C6 isolation/tuning link is implemented once in 02_POWER_3V3 (FB_C6). Do not duplicate it here.
SDIO pull-ups: CMD + DAT0..3 = 51.1k to 3V3_C6. CLK has no pull-up. Series: CLK=22R, others=0R initial.
C6 recovery remains independent of P4: UART0 TX/RX + GPIO8/GPIO9 + EN are exported to service/debug sheet.
RF: place module antenna at PCB edge; preserve official footprint keep-out on every copper layer. If enclosure blocks antenna, switch to WROOM-1U before PCB freeze.

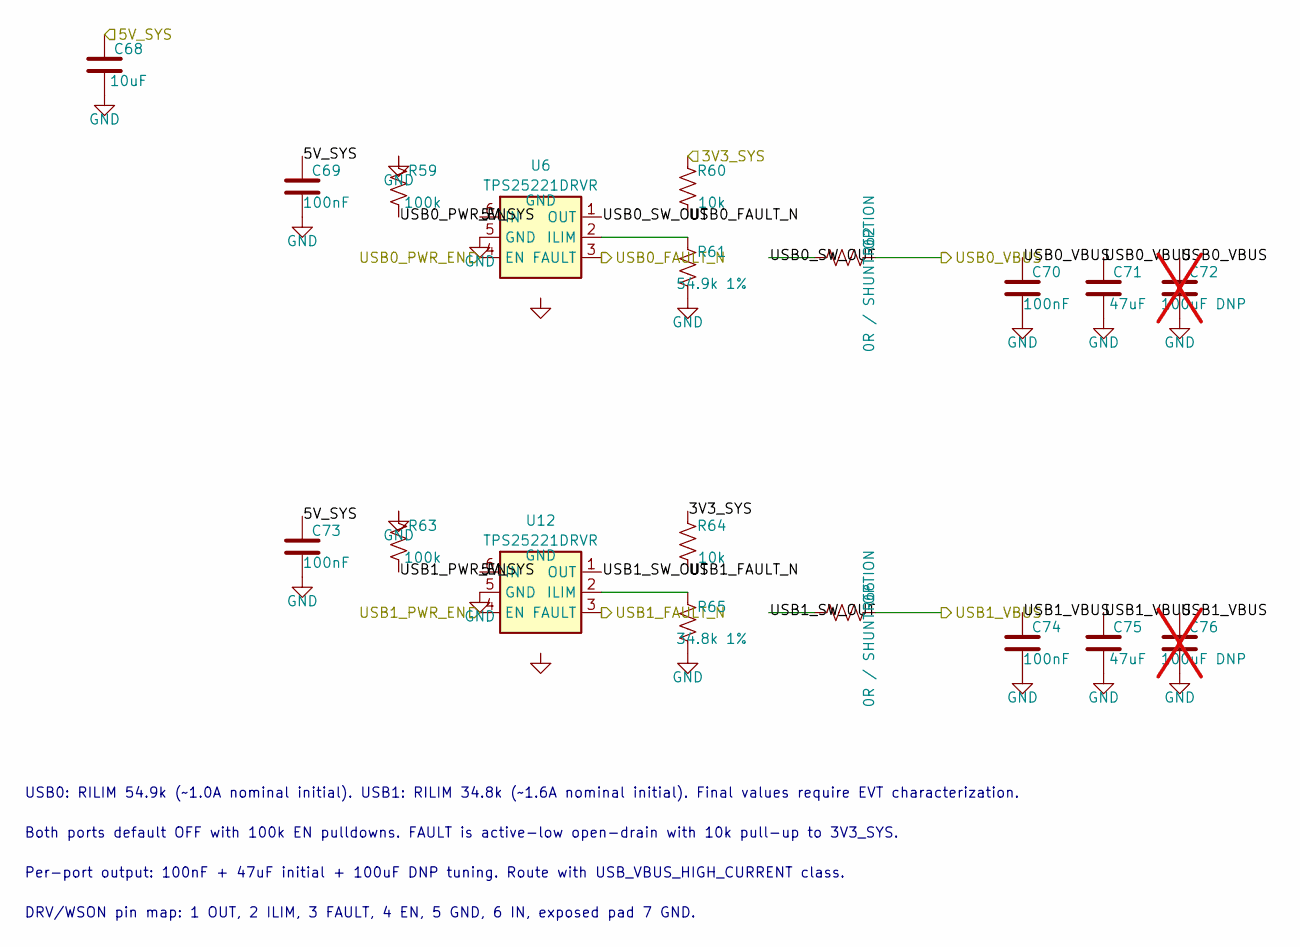
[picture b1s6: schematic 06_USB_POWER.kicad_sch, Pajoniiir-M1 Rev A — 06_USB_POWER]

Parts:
C68: 10uF; C_0805_2012Metric
C69, C70, C73, C74: 100nF; C_0603_1608Metric
C71, C75: 47uF; C_1210_3225Metric
C72, C76: 100uF DNP; C_1210_3225Metric; not fitted
R59, R63: 100k; R_0603_1608Metric
R60, R64: 10k; R_0603_1608Metric
R61: 54.9k 1%; R_0603_1608Metric
R62, R66: 0R / SHUNT OPTION; R_1206_3216Metric
R65: 34.8k 1%; R_0603_1608Metric
U6, U12: TPS25221DRVR; WSON-6-1EP_2x2mm_P0.65mm_EP1x1.6mm

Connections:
/3V3_SYS: R60.1, R64.1; also elsewhere on the board
/5V_SYS: C68.1, C69.1, C73.1, U6.6 (IN), U12.6 (IN); also elsewhere on the board
/06_USB_POWER/USB0_SW_OUT: R62.1, U6.1 (OUT)
/06_USB_POWER/USB1_SW_OUT: R66.1, U12.1 (OUT)
/USB0_FAULT_N: R60.2, U6.3 (FAULT); also elsewhere on the board
/USB0_PWR_EN: R59.2, U6.4 (EN); also elsewhere on the board
/USB0_VBUS: C70.1, C71.1, C72.1, R62.2; also elsewhere on the board
/USB1_FAULT_N: R64.2, U12.3 (FAULT); also elsewhere on the board
/USB1_PWR_EN: R63.2, U12.4 (EN); also elsewhere on the board
/USB1_VBUS: C74.1, C75.1, C76.1, R66.2; also elsewhere on the board
unnamed: R61.1, U6.2 (ILIM)
unnamed: R65.1, U12.2 (ILIM)

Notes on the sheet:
USB0: RILIM 54.9k (~1.0A nominal initial). USB1: RILIM 34.8k (~1.6A nominal initial). Final values require EVT characterization.
Both ports default OFF with 100k EN pulldowns. FAULT is active-low open-drain with 10k pull-up to 3V3_SYS.
Per-port output: 100nF + 47uF initial + 100uF DNP tuning. Route with USB_VBUS_HIGH_CURRENT class.
DRV/WSON pin map: 1 OUT, 2 ILIM, 3 FAULT, 4 EN, 5 GND, 6 IN, exposed pad 7 GND.
